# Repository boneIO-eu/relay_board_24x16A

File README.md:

# Relay Board 24x16A

Documentation you will find here: https://boneio.eu/hardware

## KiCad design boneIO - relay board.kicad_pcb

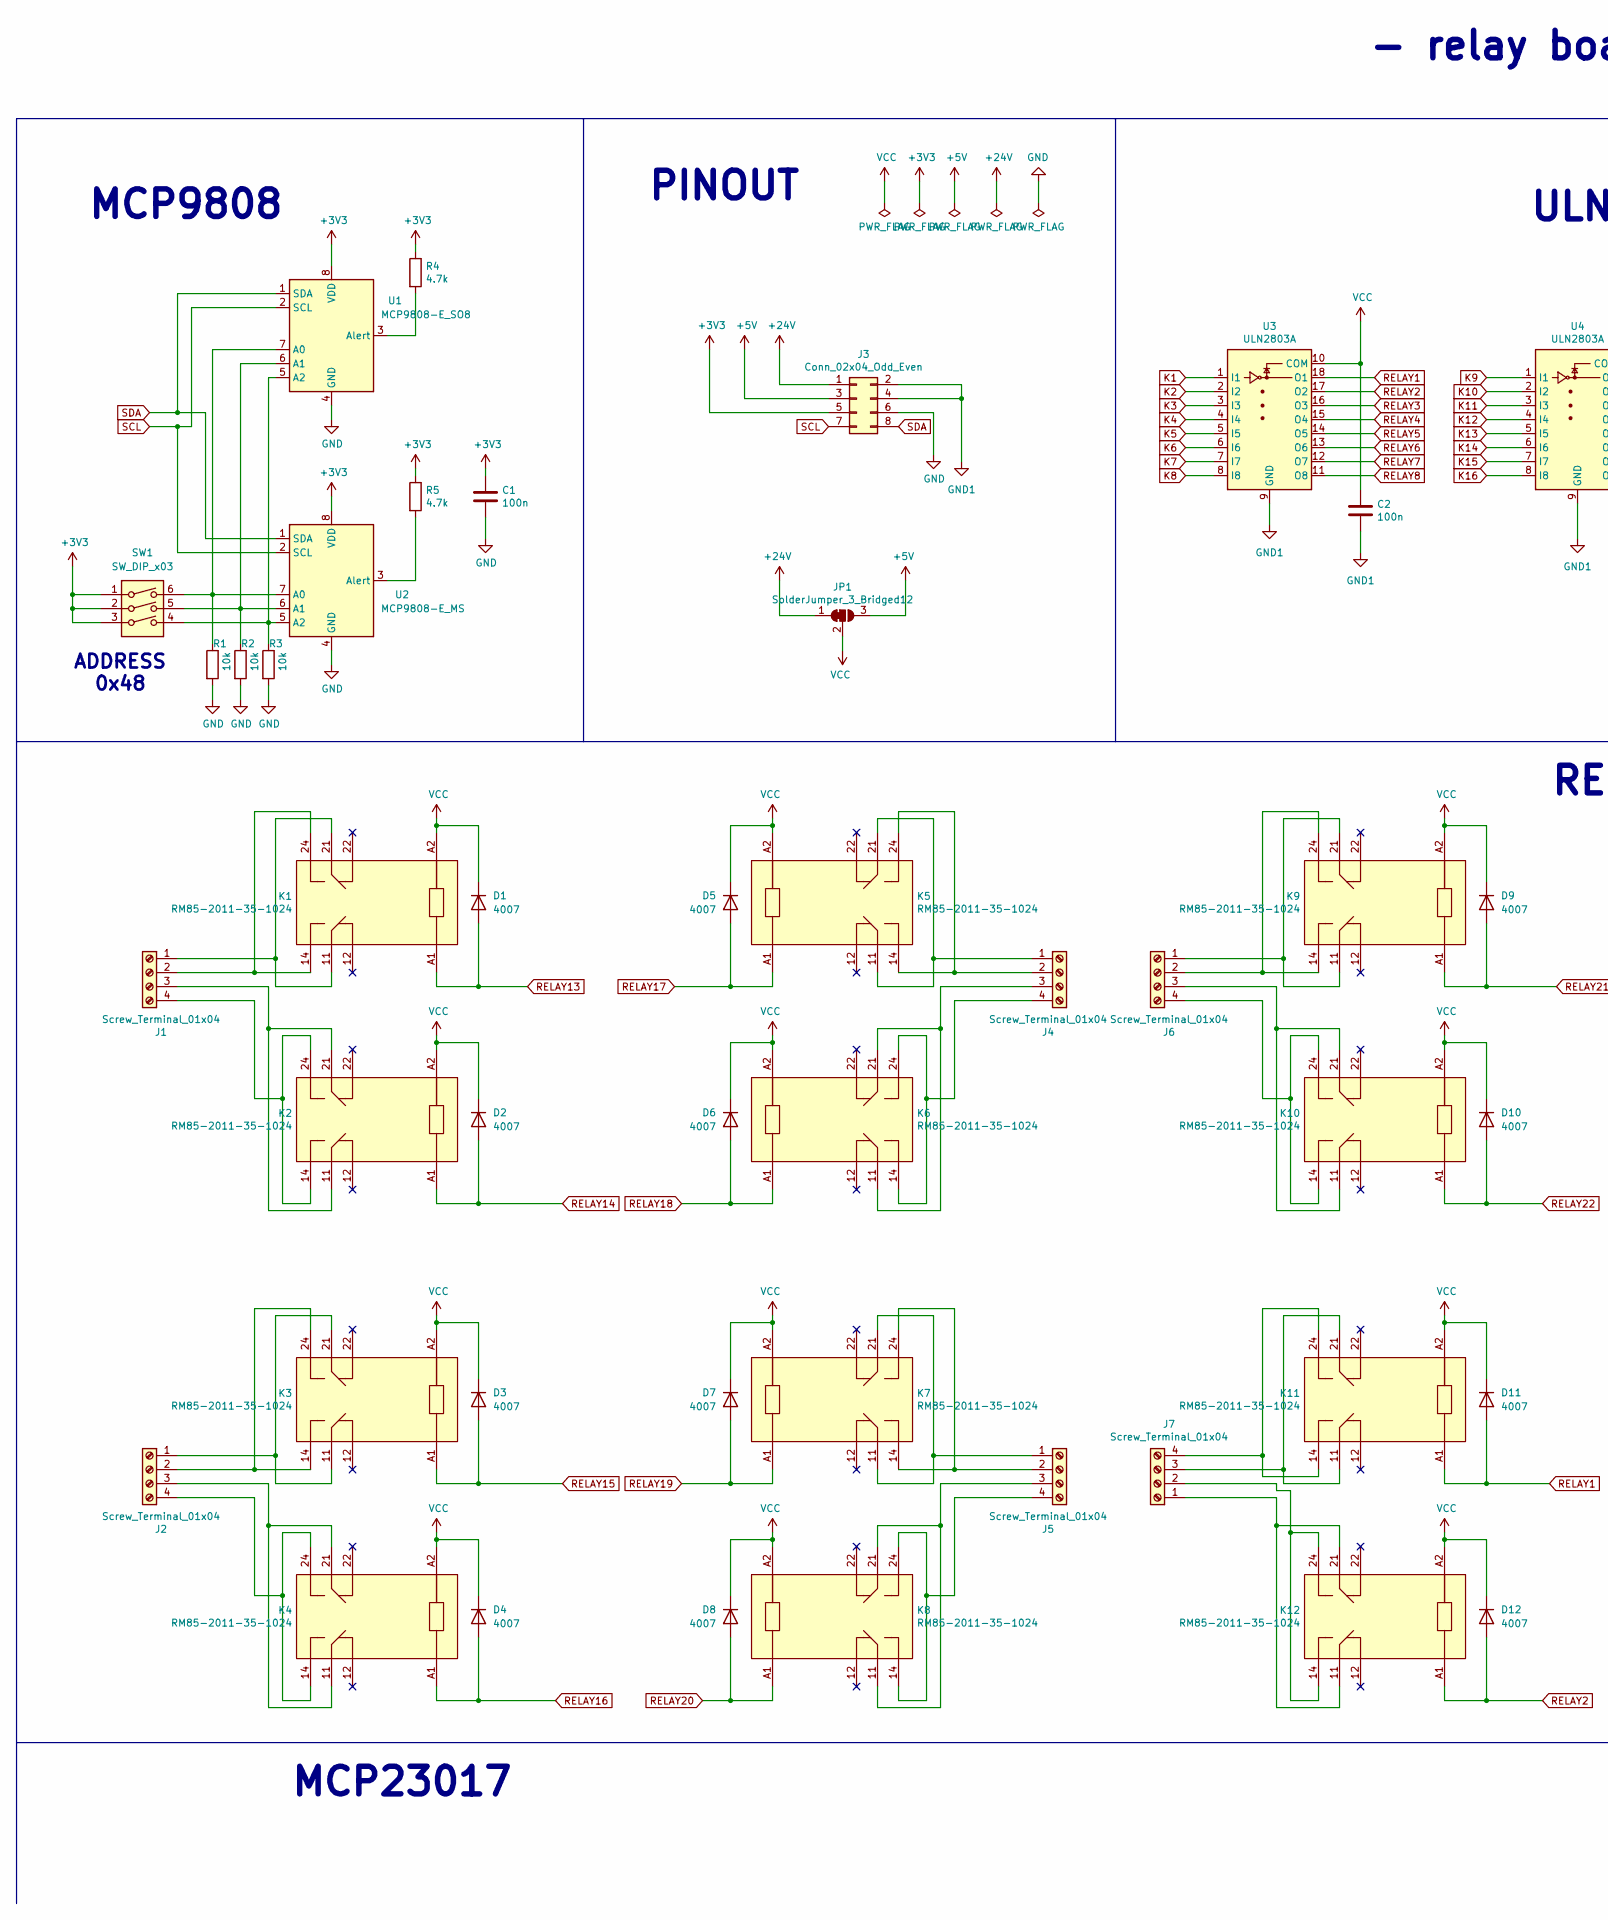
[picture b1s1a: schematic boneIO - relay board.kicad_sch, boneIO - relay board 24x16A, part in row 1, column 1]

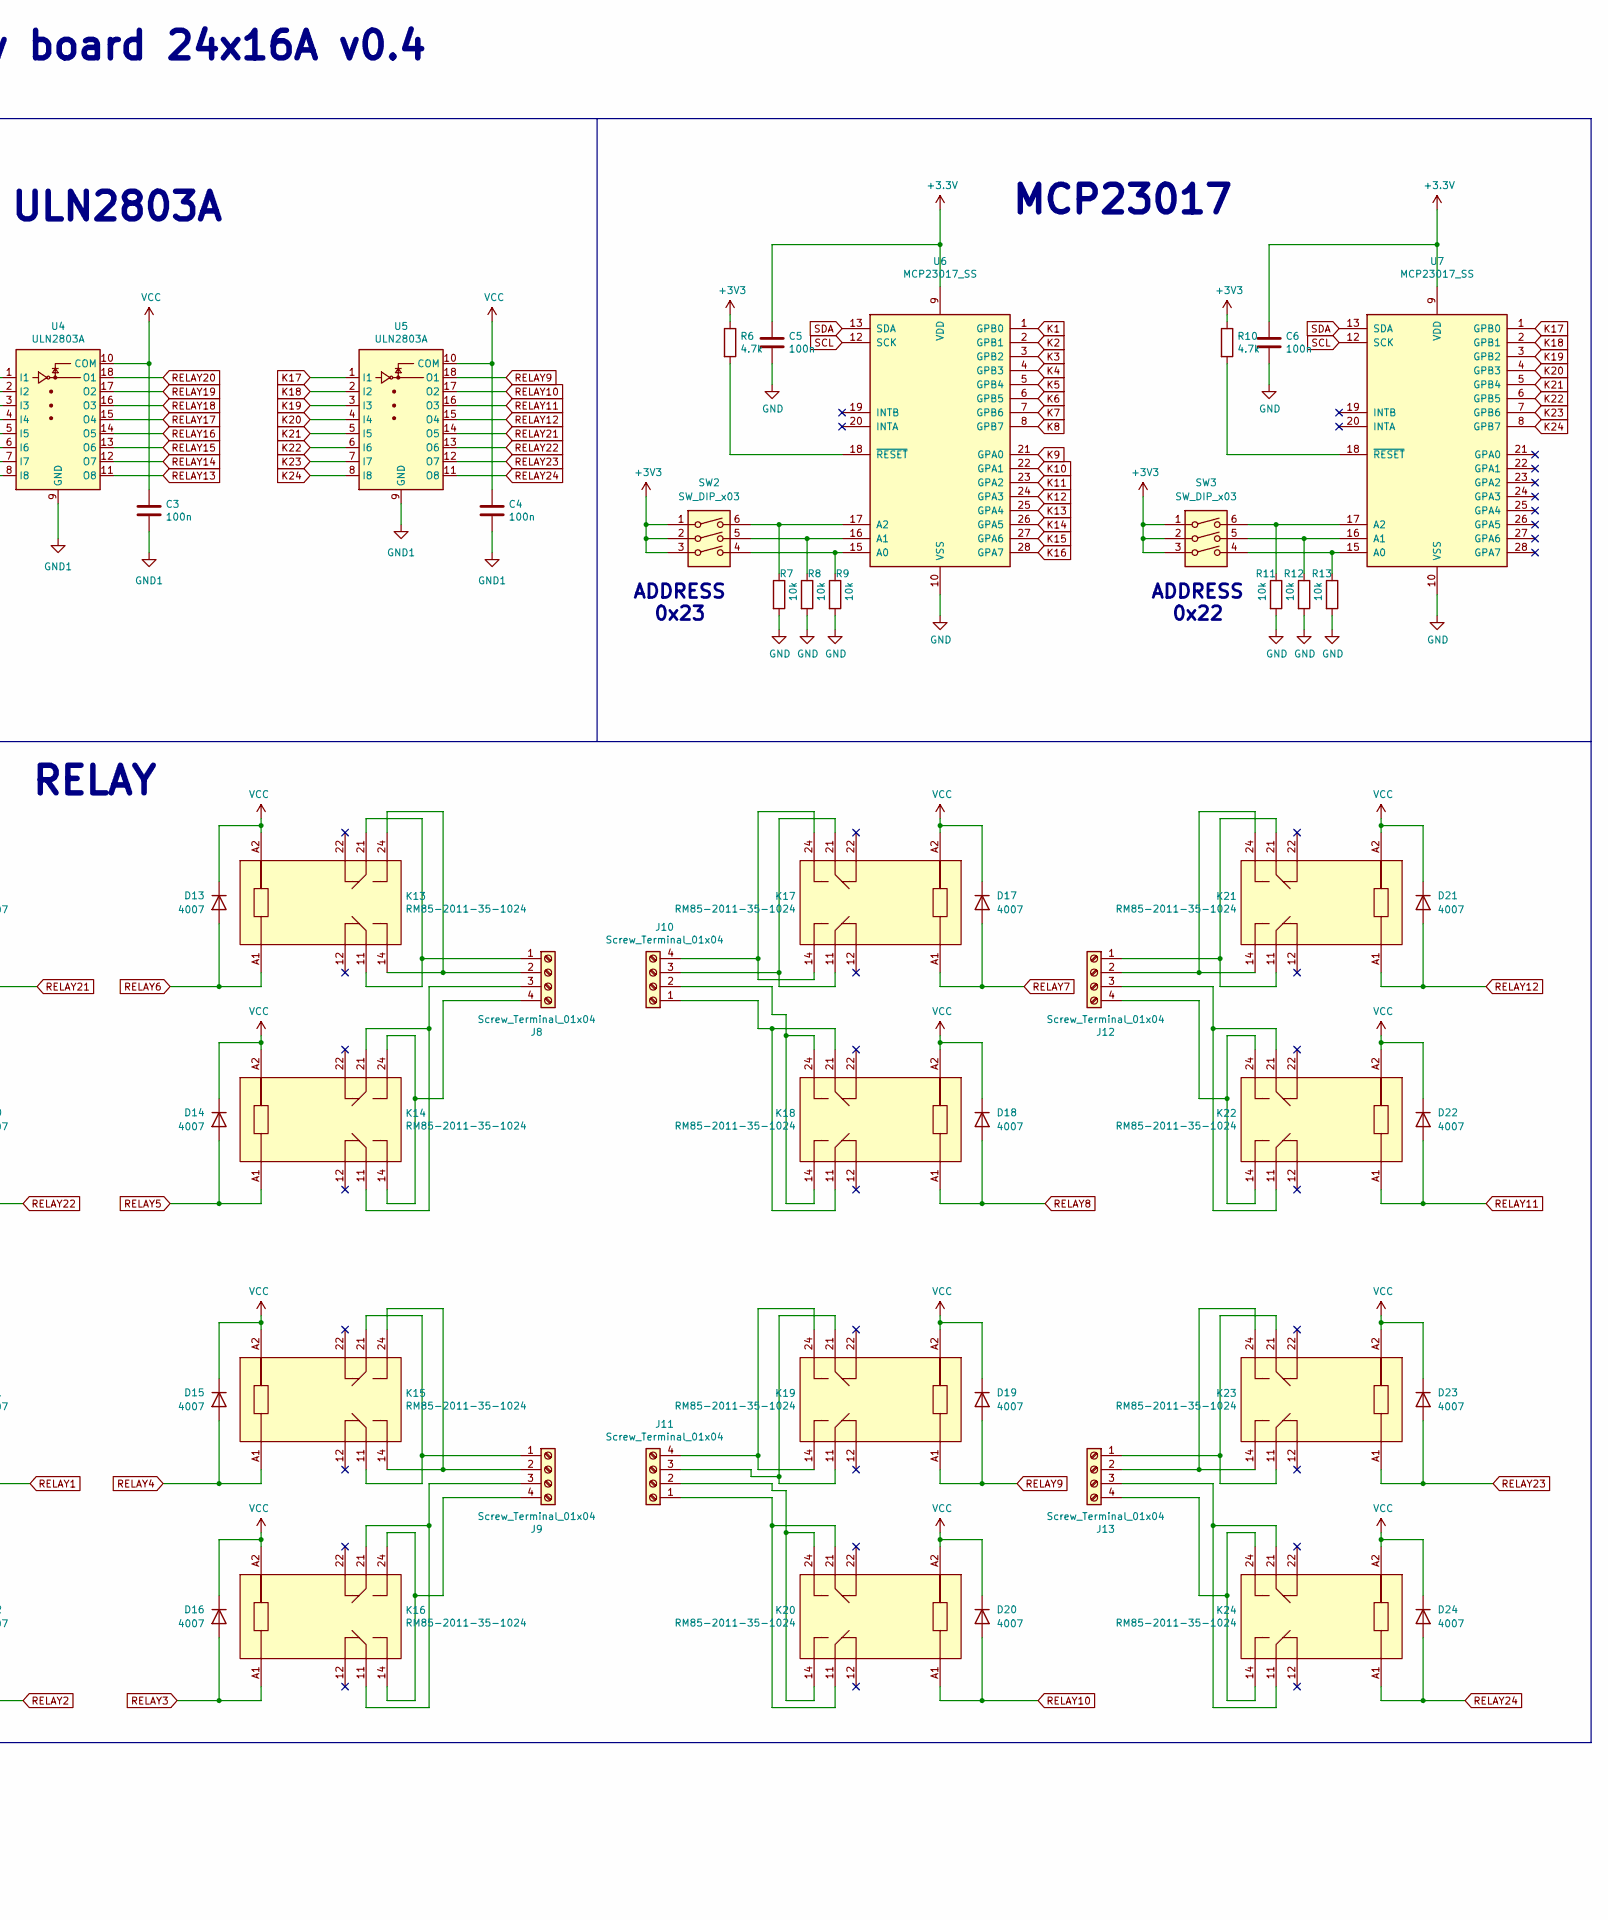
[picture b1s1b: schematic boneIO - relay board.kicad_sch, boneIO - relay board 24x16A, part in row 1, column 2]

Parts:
C1, C2, C3, C4, C5, C6: 100n; C_0603_1608Metric
D1, D2, D3, D4, D5, D6, D7, D8, D9, D10, D11, D12, D13, D14, D15, D16, D17, D18, D19, D20, D21, D22, D23, D24: 4007; D_SMA
J1, J2, J4, J5, J6, J7, J8, J9, J10, J11, J12, J13: Screw_Terminal_01x04; PhoenixContact_GMSTBA_2,5_4-G_1x04_P7.50mm_Horizontal
J3: Conn_02x04_Odd_Even; PinHeader_2x04_P2.54mm_Vertical
JP1: SolderJumper_3_Bridged12; SolderJumper-3_P1.3mm_Bridged12_RoundedPad1.0x1.5mm
K1, K2, K3, K4, K5, K6, K7, K8, K9, K10, K11, K12, K13, K14, K15, K16, K17, K18, K19, K20, K21, K22, K23, K24: RM85-2011-35-1024; RM852011351024
R1, R2, R3, R7, R8, R9, R11, R12, R13: 10k; R_0603_1608Metric
R4, R5, R6, R10: 4.7k; R_0603_1608Metric
SW1, SW2, SW3: SW_DIP_x03; SW_DIP_SPSTx03_Slide_Omron_A6S-310x_W8.9mm_P2.54mm
U1: MCP9808-E_SO8; SO-8_3.9x4.9mm_P1.27mm
U2: MCP9808-E_MS; SOP65P490X110-8N
U3, U4, U5: ULN2803A; SOIC-18W_7.5x11.6mm_P1.27mm
U6, U7: MCP23017_SS; SSOP-28_5.3x10.2mm_P0.65mm

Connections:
+5V: J3.3, JP1.3 (B)
+24V: J3.1, JP1.1 (A)
GND: C1.2, C5.2, C6.2, J3.6, R1.2, R2.2, R3.2, R7.2, R8.2, R9.2, R11.2, R12.2, R13.2, U1.4 (GND), U2.4 (GND), U6.10 (VSS), U7.10 (VSS)
GND1: C2.2, C3.2, C4.2, J3.2, J3.4, U3.9 (GND), U4.9 (GND), U5.9 (GND)
K1: U3.1 (I1), U6.1 (GPB0)
K2: U3.2 (I2), U6.2 (GPB1)
K3: U3.3 (I3), U6.3 (GPB2)
K4: U3.4 (I4), U6.4 (GPB3)
K5: U3.5 (I5), U6.5 (GPB4)
K6: U3.6 (I6), U6.6 (GPB5)
K7: U3.7 (I7), U6.7 (GPB6)
K8: U3.8 (I8), U6.8 (GPB7)
K9: U4.1 (I1), U6.21 (GPA0)
K10: U4.2 (I2), U6.22 (GPA1)
K11: U4.3 (I3), U6.23 (GPA2)
K12: U4.4 (I4), U6.24 (GPA3)
K13: U4.5 (I5), U6.25 (GPA4)
K14: U4.6 (I6), U6.26 (GPA5)
K15: U4.7 (I7), U6.27 (GPA6)
K16: U4.8 (I8), U6.28 (GPA7)
K17: U5.1 (I1), U7.1 (GPB0)
K18: U5.2 (I2), U7.2 (GPB1)
K19: U5.3 (I3), U7.3 (GPB2)
K20: U5.4 (I4), U7.4 (GPB3)
K21: U5.5 (I5), U7.5 (GPB4)
K22: U5.6 (I6), U7.6 (GPB5)
K23: U5.7 (I7), U7.7 (GPB6)
K24: U5.8 (I8), U7.8 (GPB7)
unnamed: J1.1, K1.11, K1.21
unnamed: J1.2, K1.14, K1.24
unnamed: J1.3, K2.11, K2.21
unnamed: J1.4, K2.14, K2.24
unnamed: J2.1, K3.11, K3.21
unnamed: J2.2, K3.14, K3.24
unnamed: J2.3, K4.11, K4.21
unnamed: J2.4, K4.14, K4.24
unnamed: J4.1, K5.11, K5.21
unnamed: J4.2, K5.14, K5.24
unnamed: J4.3, K6.11, K6.21
unnamed: J4.4, K6.14, K6.24
unnamed: J5.1, K7.11, K7.21
unnamed: J5.2, K7.14, K7.24
unnamed: J5.3, K8.11, K8.21
unnamed: J5.4, K8.14, K8.24
unnamed: J6.1, K9.11, K9.21
unnamed: J6.2, K9.14, K9.24
unnamed: J6.3, K10.11, K10.21
unnamed: J6.4, K10.14, K10.24
unnamed: J7.1, K12.11, K12.21
unnamed: J7.2, K12.14, K12.24
unnamed: J7.3, K11.11, K11.21
unnamed: J7.4, K11.14, K11.24
unnamed: J8.1, K13.11, K13.21
unnamed: J8.2, K13.14, K13.24
unnamed: J8.3, K14.11, K14.21
unnamed: J8.4, K14.14, K14.24
unnamed: J9.1, K15.11, K15.21
unnamed: J9.2, K15.14, K15.24
unnamed: J9.3, K16.11, K16.21
unnamed: J9.4, K16.14, K16.24
unnamed: J10.1, K18.11, K18.21
unnamed: J10.2, K18.14, K18.24
unnamed: J10.3, K17.11, K17.21
unnamed: J10.4, K17.14, K17.24
unnamed: J11.1, K20.11, K20.21
unnamed: J11.2, K20.14, K20.24
unnamed: J11.3, K19.11, K19.21
unnamed: J11.4, K19.14, K19.24
unnamed: J12.1, K21.11, K21.21
unnamed: J12.2, K21.14, K21.24
unnamed: J12.3, K22.11, K22.21
unnamed: J12.4, K22.14, K22.24
unnamed: J13.1, K23.11, K23.21
unnamed: J13.2, K23.14, K23.24
unnamed: J13.3, K24.11, K24.21
unnamed: J13.4, K24.14, K24.24
unnamed: R1.1, SW1.6, U1.7 (A0), U2.7 (A0)
unnamed: R2.1, SW1.5, U1.6 (A1), U2.6 (A1)
unnamed: R3.1, SW1.4, U1.5 (A2), U2.5 (A2)
unnamed: R4.2, U1.3 (Alert)
unnamed: R5.2, U2.3 (Alert)
unnamed: R6.2, U6.18 (~RESET)
unnamed: R7.1, SW2.6, U6.17 (A2)
unnamed: R8.1, SW2.5, U6.16 (A1)
unnamed: R9.1, SW2.4, U6.15 (A0)
unnamed: R10.2, U7.18 (~RESET)
unnamed: R11.1, SW3.6, U7.17 (A2)
unnamed: R12.1, SW3.5, U7.16 (A1)
unnamed: R13.1, SW3.4, U7.15 (A0)
RELAY1: D11.1 (A), K11.A1, U3.18 (O1)
RELAY2: D12.1 (A), K12.A1, U3.17 (O2)
RELAY3: D16.1 (A), K16.A1, U3.16 (O3)
RELAY4: D15.1 (A), K15.A1, U3.15 (O4)
RELAY5: D14.1 (A), K14.A1, U3.14 (O5)
RELAY6: D13.1 (A), K13.A1, U3.13 (O6)
RELAY7: D17.1 (A), K17.A1, U3.12 (O7)
RELAY8: D18.1 (A), K18.A1, U3.11 (O8)
RELAY9: D19.1 (A), K19.A1, U5.18 (O1)
RELAY10: D20.1 (A), K20.A1, U5.17 (O2)
RELAY11: D22.1 (A), K22.A1, U5.16 (O3)
RELAY12: D21.1 (A), K21.A1, U5.15 (O4)
RELAY13: D1.1 (A), K1.A1, U4.11 (O8)
RELAY14: D2.1 (A), K2.A1, U4.12 (O7)
RELAY15: D3.1 (A), K3.A1, U4.13 (O6)
RELAY16: D4.1 (A), K4.A1, U4.14 (O5)
RELAY17: D5.1 (A), K5.A1, U4.15 (O4)
RELAY18: D6.1 (A), K6.A1, U4.16 (O3)
RELAY19: D7.1 (A), K7.A1, U4.17 (O2)
RELAY20: D8.1 (A), K8.A1, U4.18 (O1)
RELAY21: D9.1 (A), K9.A1, U5.14 (O5)
RELAY22: D10.1 (A), K10.A1, U5.13 (O6)
RELAY23: D23.1 (A), K23.A1, U5.12 (O7)
RELAY24: D24.1 (A), K24.A1, U5.11 (O8)
SCL: J3.7, U1.2 (SCL), U2.2 (SCL), U6.12 (SCK), U7.12 (SCK)
SDA: J3.8, U1.1 (SDA), U2.1 (SDA), U6.13 (SDA), U7.13 (SDA)
VCC: C2.1, C3.1, C4.1, D1.2 (K), D2.2 (K), D3.2 (K), D4.2 (K), D5.2 (K), D6.2 (K), D7.2 (K), D8.2 (K), D9.2 (K), D10.2 (K), D11.2 (K), D12.2 (K), D13.2 (K), D14.2 (K), D15.2 (K), D16.2 (K), D17.2 (K), D18.2 (K), D19.2 (K), D20.2 (K), D21.2 (K), D22.2 (K), D23.2 (K), D24.2 (K), JP1.2 (C), K1.A2, K2.A2, K3.A2, K4.A2, K5.A2, K6.A2, K7.A2, K8.A2, K9.A2, K10.A2, K11.A2, K12.A2, K13.A2, K14.A2, K15.A2, K16.A2, K17.A2, K18.A2, K19.A2, K20.A2, K21.A2, K22.A2, K23.A2, K24.A2, U3.10 (COM), U4.10 (COM), U5.10 (COM)

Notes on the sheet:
MCP23017
ADDRESS 0x48
ADDRESS 0x23
PINOUT
ADDRESS 0x22
ULN2803A
- relay board 24x16A v0.4
RELAY
MCP9808

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
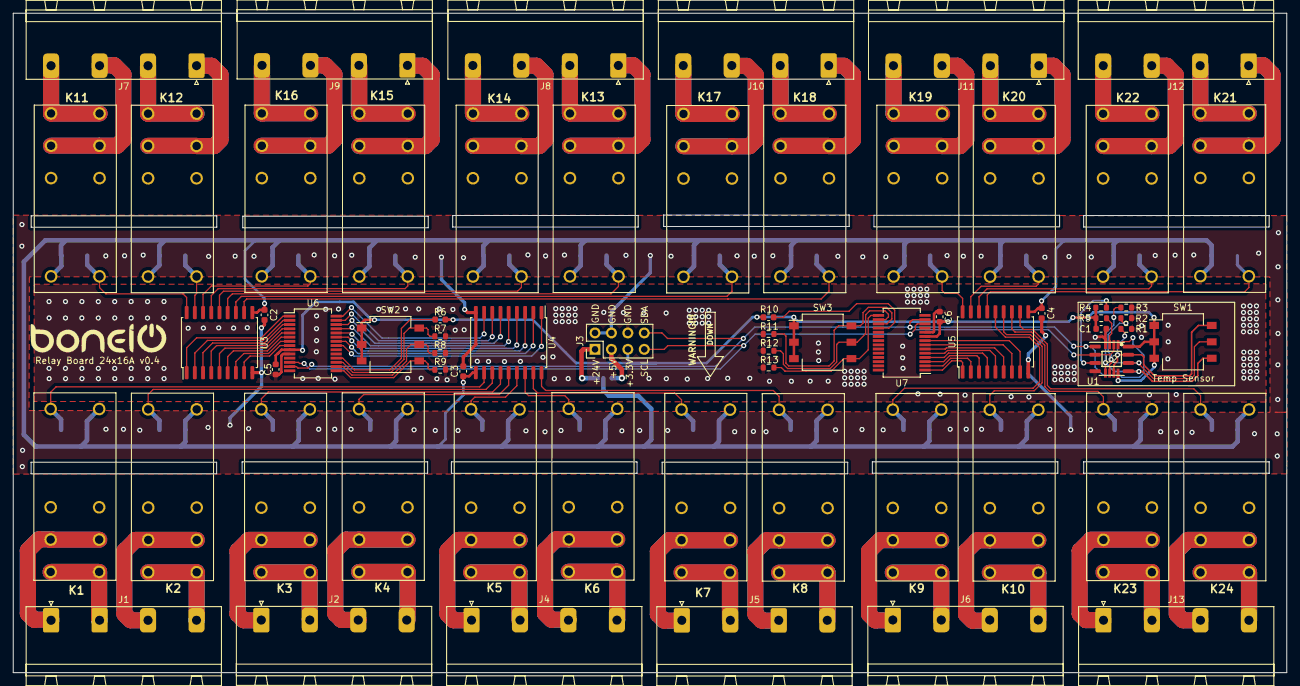
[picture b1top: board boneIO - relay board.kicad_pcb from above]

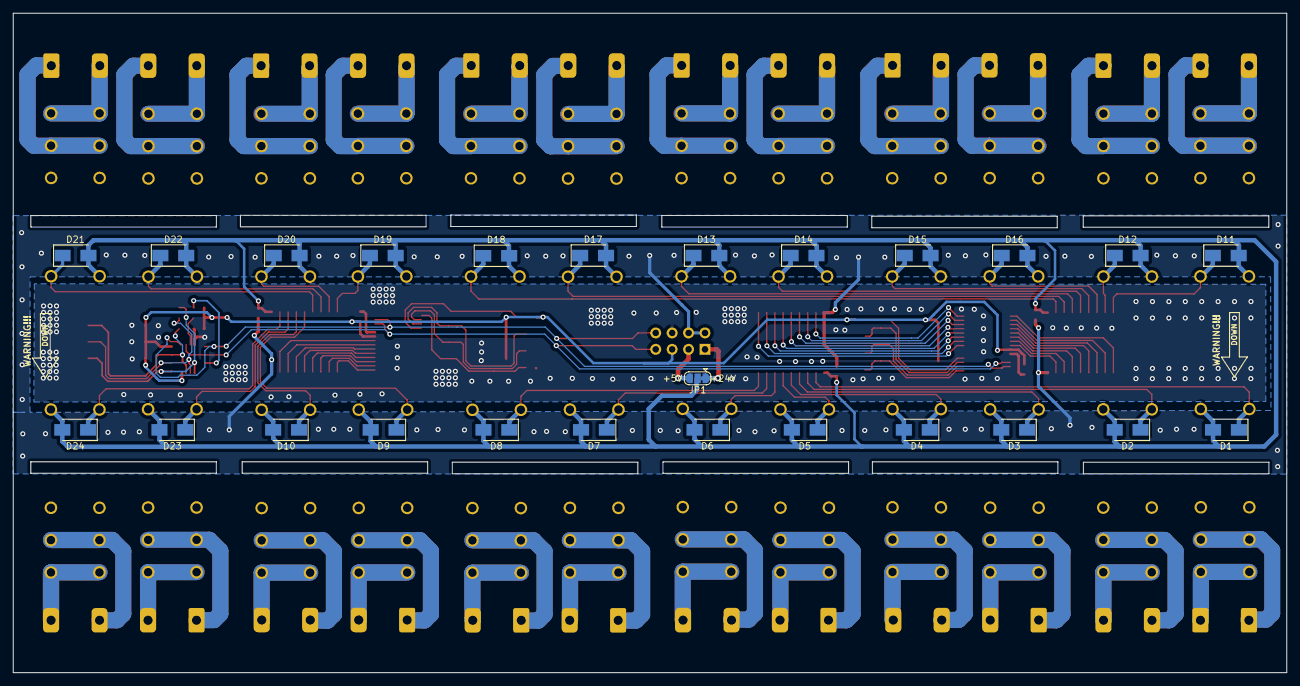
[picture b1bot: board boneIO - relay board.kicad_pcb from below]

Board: 2 copper layers, 197.0 x 102.0 mm, 91 parts (25 on the bottom side), 117 nets.

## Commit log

2021-11-03 Changed directory name for 24x16A
2021-11-07 Fixed some DRC bugs on schema, and changed directory name to 24x16A
2021-11-07 DRC Cleanup and some other small fixes
2021-11-07 Some more small fixes
2021-11-08 final PCB version
2021-11-10 merge
2021-11-10 cleanup relay board 24x16
2021-11-10 Changed board labels
2021-11-19 correcting the scheme
2021-11-24 24x16 cleanup
2021-11-25 Relay model fixed
2021-12-04 24x16 v0.3
2021-12-18 Changed place of K labels
2022-01-17 Directory cleanup
2022-01-17 Create LICENSE
2022-05-18 relay board 24x16A v0.4
2022-05-19 added gitignore
2022-05-21 Added readme and some cleanup
2022-05-23 relay board 24x16A v0.4 (rev2)
